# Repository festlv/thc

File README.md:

Homebrew plasma cutter torch height controller
--------------------------------------------------

Schematics, layout and code for a simple yet intelligent replacement for THC301d
torch height controller.

The main difference is that this one samples cutting voltage automatically
after cut is started, and then tries to keep the plasma torch at the same
height.

Beware- this has only been tested for a few hours as of now, but the results
seem to be as good as with THC301d (but setpoint is determined automatically).

License: GNU General Public License (GPL) version 3.

Author: Reinis Veips, http://wot.lv/

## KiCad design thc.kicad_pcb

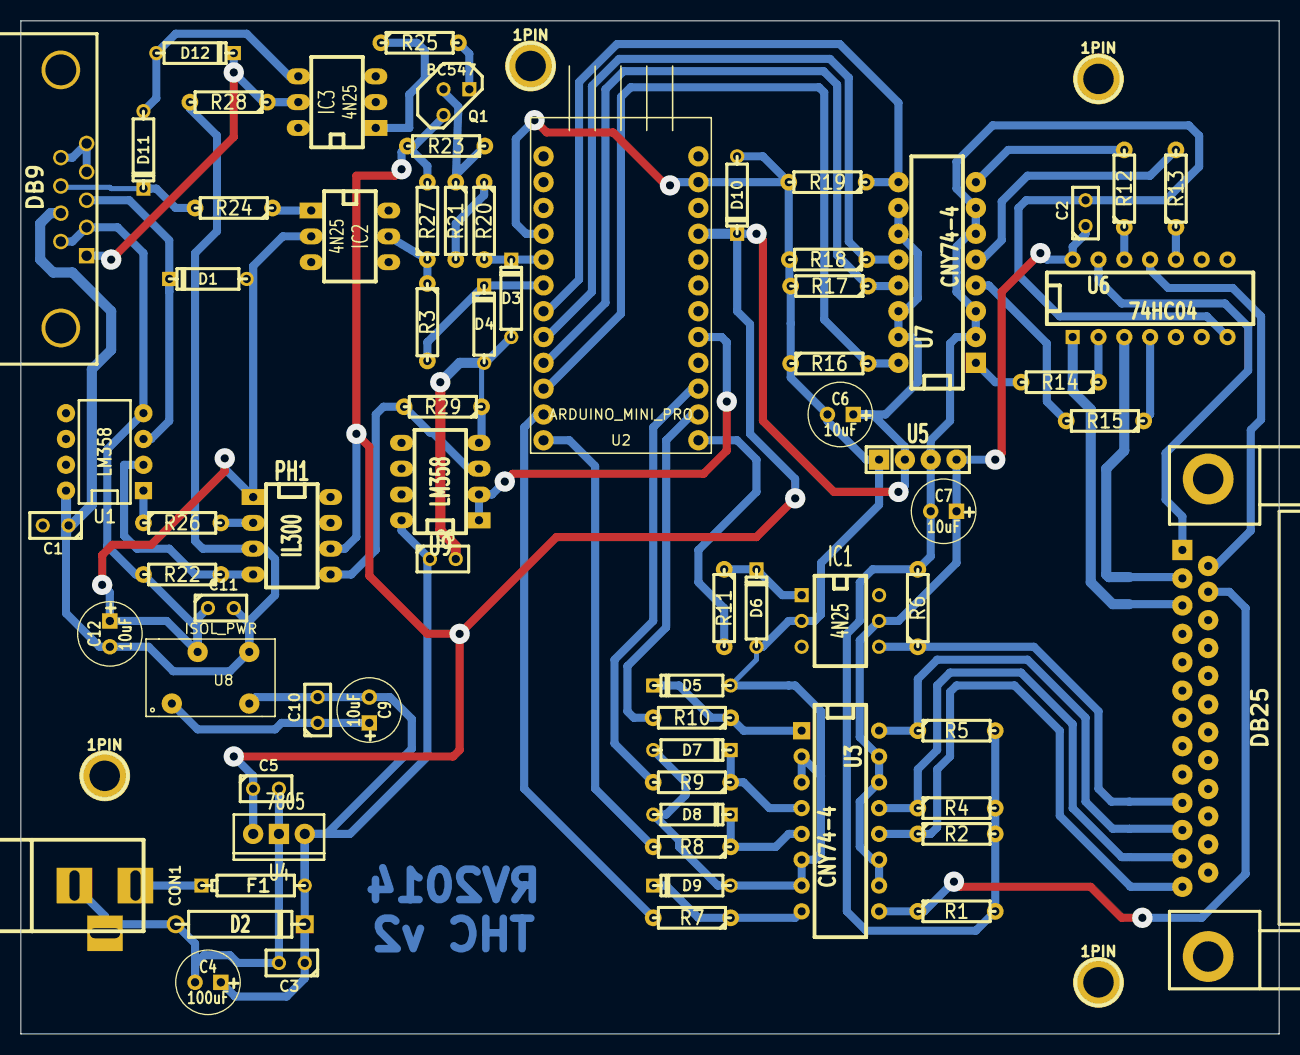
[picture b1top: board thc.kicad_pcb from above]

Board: 2 copper layers, 123.8 x 99.7 mm, 75 parts (0 on the bottom side), 55 nets.

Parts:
1PIN, 1PIN#2, 1PIN#3, 1PIN#4: P***; 1pin
C1, C8, C10, C11: 0.1uF; C1
C2, C3, C5: 1uF; C1
C4: 100uF; C1V7
C6, C7, C9, C12: 10uF; C1V7
CON1: BARREL_JACK
D1, D3, D4, D5, D6, D7, D8, D9, D10: 5v1 ZENER; D3
D2: 1N4007; D5
D11, D12: 12v1 ZENER; D3
F1: PTC 1.1A 30V; CP4
IC1: 4N25; DIP-6__300
IC2, IC3: 4N25; DIP-6__300_ELL
J2: DB25; DB25FC
J3: DB9; DB9FC
PH1: IL300; DIP-8__300_ELL
Q1: BC547; TO92-EBC
R1, R2, R4, R5, R6, R16, R17, R18, R19, R23: 10K; R3-LARGE_PADS
R3, R20, R25: 100R; R3-LARGE_PADS
R7, R8, R9, R10, R11, R12, R13, R14, R15: 200R; R3-LARGE_PADS
R21: 3K3; R3-LARGE_PADS
R22, R29: 47k; R3-LARGE_PADS
R24, R26: 400R; R3-LARGE_PADS
R27, R28: 1K; R3-LARGE_PADS
U1: LM358; DIP-8__300
U2: ARDUINO_MINI_PRO; ARDUINO_MINI
U3, U7: CNY74-4; DIP-16__300
U4: 7805; LM78XXV
U5: ISOL_PWR; SIL-4
U6: 74HC04; DIP-14__300
U8: ISOL_PWR; MCE_DIP
U9: LM358; DIP-8__300_ELL

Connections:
+5V: C5.1, C6.1, D10.2, PH1.6, Q1.1, R23.2, R27.2, U2.25, U4.VO, U5.2, U7.10, U7.11, U7.14, U7.15
+5VA: C2.1, C7.1, IC1.5, U3.10, U3.11, U3.14, U3.15, U5.4, U6.14
+12C: C1.1, C11.2, C12.2, J3.7, PH1.3, R28.2, U1.8, U8.4
+12V: C3.1, C4.1, C8.1, C9.2, C10.2, D2.2, F1.2, U4.VI, U8.2, U9.8
/Isolation/U_THC_INP1: J2.1, U6.13
/Isolation/U_THC_INP2: J2.14, U6.11
/Isolation/U_THC_INP3: J2.2, U6.3
/Isolation/U_THC_INP4: J2.3, U6.1
/Isolation/U_THC_OUT1: J2.15, R1.1, U3.9
/Isolation/U_THC_OUT2: IC1.4, J2.10, R6.1
/Isolation/U_THC_OUT3: J2.11, R5.1, U3.16
/Isolation/U_THC_OUT4: J2.12, R4.1, U3.13
/Isolation/U_THC_OUT5: J2.13, R2.1, U3.12
/Plasma source/ANALOG_IN: D1.2, J3.3, U1.3
/Plasma source/ARC_OK: D11.2, J3.8, R24.2
/Plasma source/TORCH_ON: D12.2, IC3.5, J3.1, R28.1
GND: C3.2, C4.2, C5.2, C6.2, C8.2, C9.1, C10.1, CON1.2, CON1.3, D2.1, D3.1, D4.1, D5.1, D6.1, D7.1, D8.1, D9.1, D10.1, IC1.2, IC2.4, IC3.2, R16.1, R17.2, R18.2, R19.2, R29.1, U2.4, U2.27, U3.2, U3.3, U3.6, U3.7, U4.GND, U5.1, U8.1, U9.4
GNDA: C2.2, C7.2, J2.18, J2.19, J2.20, J2.21, J2.22, J2.23, J2.24, J2.25, R1.2, R2.2, R4.2, R5.2, R6.2, U5.3, U6.7, U7.2, U7.3, U7.6, U7.7
I_ANALOG_IN: U2.21, U9.1, U9.2
I_ARC_OK: IC2.5, R3.1, R27.1
I_THC_INP1: R19.1, U2.7, U7.9
I_THC_INP2: R18.1, U2.8, U7.12
I_THC_INP3: R17.1, U2.9, U7.13
I_THC_INP4: R16.2, U2.10, U7.16
I_THC_OUT1: R7.2, U2.11
I_THC_OUT2: R11.2, U2.17
I_THC_OUT3: R10.2, U2.18
I_THC_OUT4: R9.2, U2.19
I_THC_OUT5: R8.2, U2.12
I_TORCH_ON: R20.1, R21.2
unnamed: D3.2, R20.2, U2.5
unnamed: D4.2, R3.2, U2.6
unnamed: CON1.1, F1.1
unnamed: D6.2, IC1.1, R11.1
unnamed: R14.2, U7.1
unnamed: R12.2, U7.8
unnamed: R13.2, U7.5
unnamed: R15.2, U7.4
unnamed: R12.1, U6.12
unnamed: R13.1, U6.10
unnamed: R14.1, U6.2
unnamed: R15.1, U6.4
unnamed: D9.2, R7.1, U3.8
unnamed: D8.2, R8.1, U3.5
unnamed: D7.2, R9.1, U3.4
unnamed: D5.2, R10.1, U3.1
unnamed: Q1.2, R21.1, R23.1
unnamed: IC3.1, R25.1
unnamed: Q1.3, R25.2
unnamed: IC2.1, R24.1
unnamed: PH1.4, R22.1, U1.2
unnamed: R26.1, U1.1
unnamed: PH1.2, R26.2
unnamed: PH1.5, R29.2, U9.3
VSS: C1.2, C11.1, C12.1, D1.1, D11.1, D12.1, IC2.2, IC3.4, J3.2, J3.4, J3.5, J3.6, J3.9, PH1.1, R22.2, U1.4, U8.3

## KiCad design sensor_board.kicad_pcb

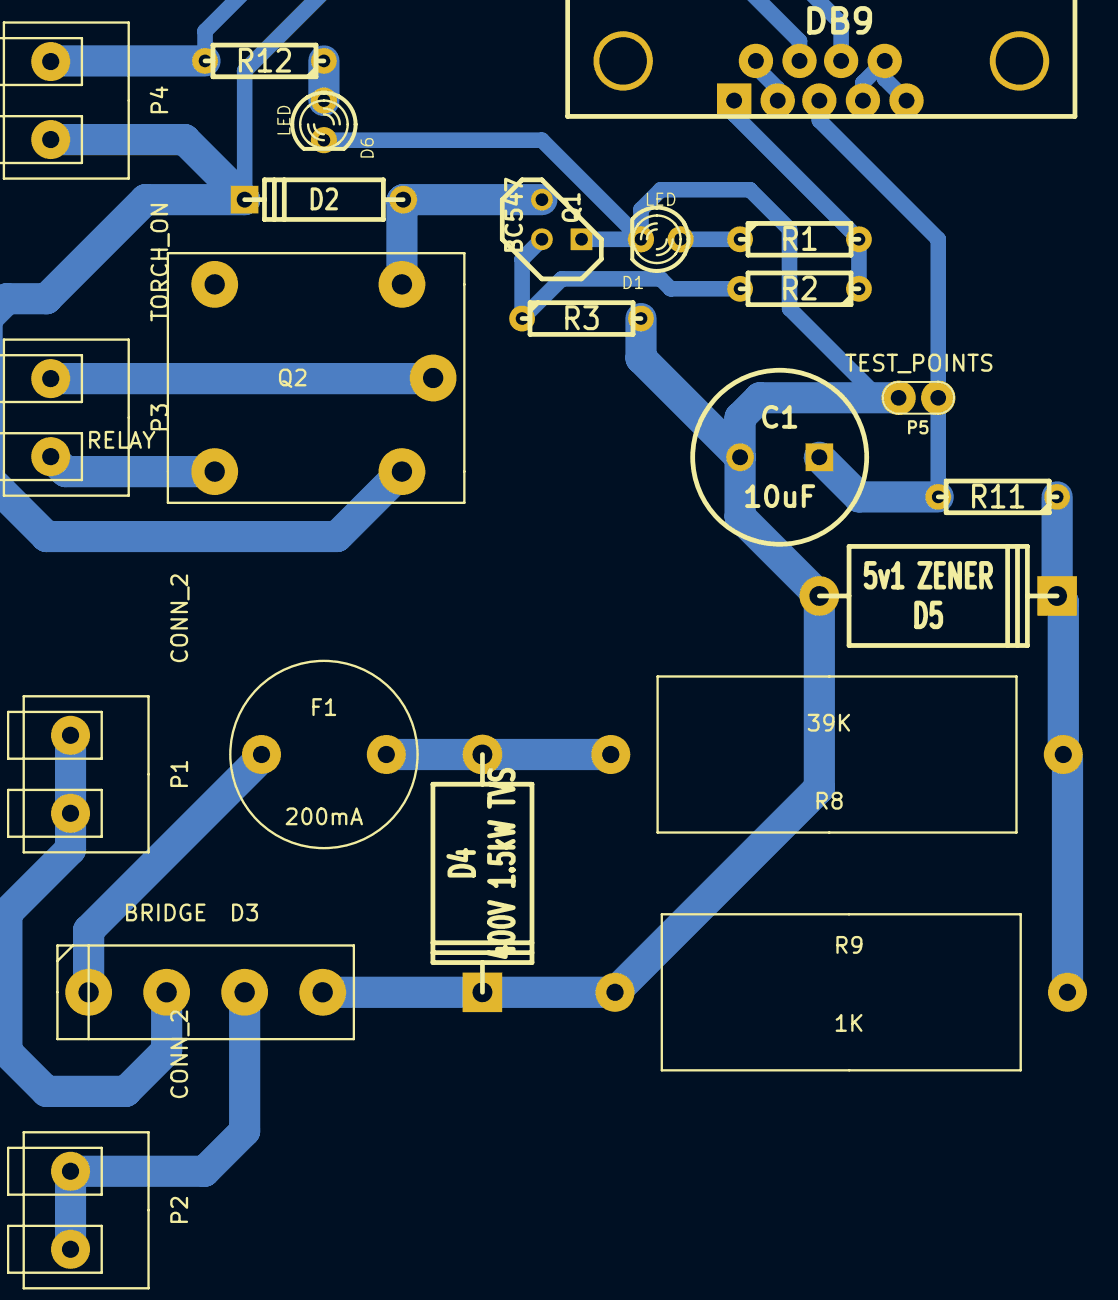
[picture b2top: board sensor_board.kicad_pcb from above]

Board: 2 copper layers, 23 parts (0 on the bottom side), 16 nets.

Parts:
C1: 10uF; C2V10
D1, D6: LED; LED-3MM
D2: DIODE; D4
D3: BRIDGE
D4: 400V 1.5kW TVS; D6
D5: 5v1 ZENER; D6
F1: 200mA; ROUND_FUSE_HOLDER
J1: DB9; DB9FC
P1, P2: CONN_2; SCREW_TERM_2
P3: TORCH_ON; SCREW_TERM_2
P4: ARC_OK; SCREW_TERM_2
P5: TEST_POINTS; TEST_POINT_2PADS
Q1: BC547; TO92-CBE
Q2: RELAY; FINDER_RELAY
R1: 3K3; R3-LARGE_PADS
R2: 1K; R3-LARGE_PADS
R3: 20K; R3-LARGE_PADS
R8: 39K; R_5W_AXIAL
R9: 1K; R_5W_AXIAL
R11: 100R; R3-LARGE_PADS
R12: 3K; R3-LARGE_PADS

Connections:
+12V: D2.2, J1.7, P4.2, Q2.1
/ARC_OK: J1.8, P4.1, R12.2
/FILT_SIG: C1.1, J1.3, P5.1, R11.2
/TORCH_ON: J1.1, R1.2, R2.1
GND: C1.2, D1.2, D3.1, D4.2, D5.1, D6.2, J1.2, J1.4, J1.5, J1.6, J1.9, J1.10, P5.2, Q1.3, R3.2, R9.2
unnamed: D6.1, R12.1
unnamed: D1.1, R1.1
unnamed: D3.3, F1.1
unnamed: D5.2, R8.2, R9.1, R11.1
unnamed: D3.2, P2.1, P2.2
unnamed: D4.1, F1.2, R8.1
unnamed: Q1.2, R2.2, R3.1
unnamed: D2.1, Q1.1, Q2.2
unnamed: D3.4, P1.1, P1.2
unnamed: P3.1, Q2.3
unnamed: P3.2, Q2.5

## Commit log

2013-12-28 Committing changes
2013-12-28 Hopefully finished sensor board, started to work on PC interface board
2013-12-28 Increased size for some of the holes
2013-12-29 Started work on thc board itself
2013-12-29 Finished controller board
2014-01-13 Finalized design, produced PCB, started testing it
2014-01-13 Done some more tests
2014-01-17 Fixes completely wrong schematics and PCB layout
2014-01-19 Started first revision of software
2014-01-19 Fixed sensor board schematics- it's not wise to power relay from regulator
2014-01-20 Fixed wrong power pin being used in Atmega
2014-01-21 Updated load resistor values in schematics
2014-01-21 Code is now approximately ready for real-life testing
2014-02-02 Committed latest revision of schematics before revamp
2014-02-02 Finished sensor board, started layout of controller board
2014-02-12 Finalized new PCB
2014-02-17 Changed sensor board to contain less resistors
2014-02-17 Added Zener diodes on IO from plasma source
2014-02-24 Changed Q1 pulldown to pullup, fixed it's pinout
2014-03-01 Inverted logic for torch on relay control, removed debugging code
2014-03-02 Updated defines
2014-03-02 Cleaned up schematics
2014-03-02 Removed unneccessary cruft
2014-03-02 Added readme
